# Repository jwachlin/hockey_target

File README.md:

# Interactive Electronic Hockey Targets
Hardware and firmware for interactive electronic hockey targets

To be used for hockey shooting training. More details at https://hackaday.io/project/169424-interactive-electronic-hockey-targets

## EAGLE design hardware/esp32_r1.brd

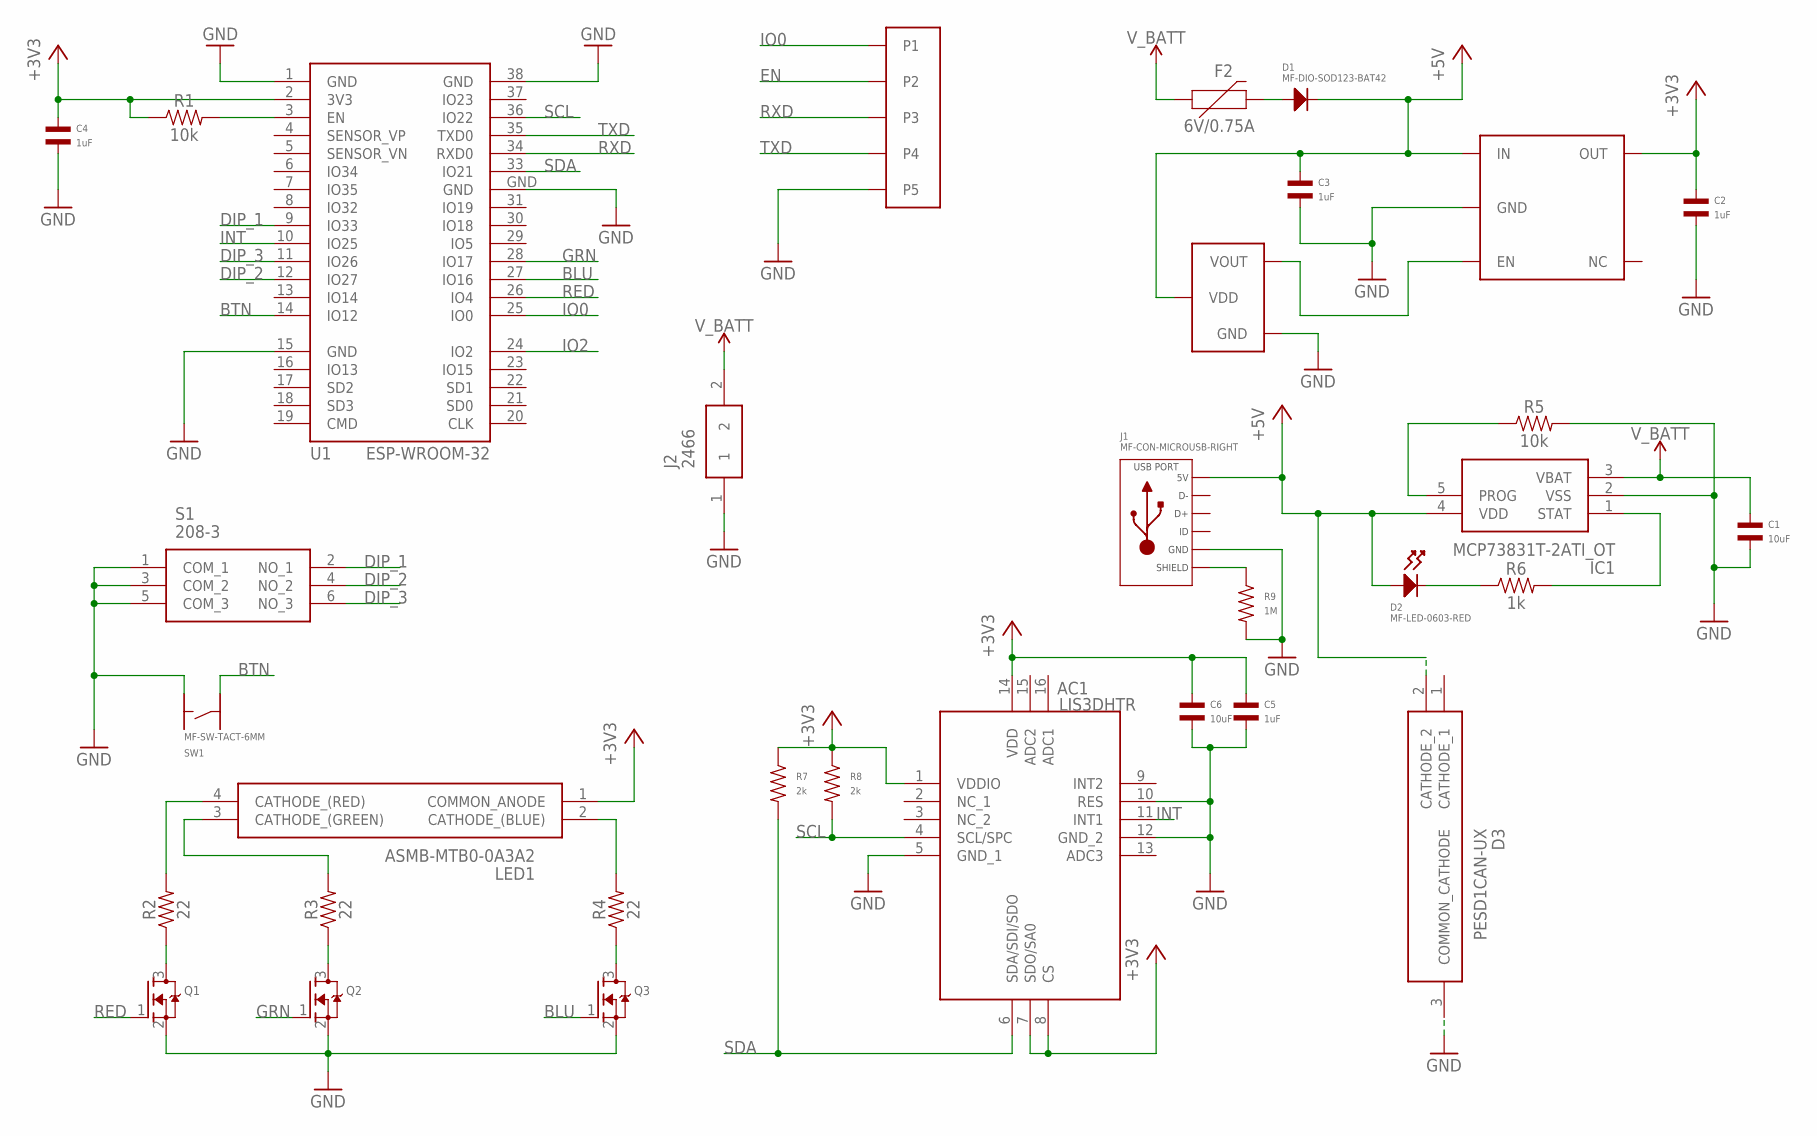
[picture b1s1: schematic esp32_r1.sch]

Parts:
AC1: LIS3DHTR; PQFN50P300X300X100-16N
C1, C6: 10uF; C1206
C2, C3, C4, C5: 1uF; C0402
D1: MF-DIO-SOD123-BAT42; SOD-123
D2: MF-LED-0603-RED; LED0603
D3: PESD1CAN-UX; SOT95P230X110-3N
F2: 6V/0.75A; 1206
IC1: MCP73831T-2ATI_OT; SOT95P270X145-5N
J1: MF-CON-MICROUSB-RIGHT; MICROUSB-RIGHT
J2: 2466
LED1: ASMB-MTB0-0A3A2; AVAGO_PLCC4
Q1, Q2, Q3: MOSFET-NREFLOW; SOT23-R
R1, R5: 10k; 0402
R2, R3, R4: 22; 0402
R6: 1k; 0402
R7, R8: 2k; R0402
R9: 1M; R0402
S1: 208-3; 2083
SW1: MF-SW-TACT-6MM; TACT6MM
U1: ESP-WROOM-32
U4: TLV755; SOT23-DBV
U6: 53047; PICOBLADE_53047
U7: BD49K33G; SSOP3

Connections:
+3V3: AC1.1 (VDDIO), AC1.7 (SDO/SA0), AC1.8 (CS), AC1.14 (VDD), C2.P$1, C4.P$1, C5.P$1, C6.P$1, LED1.1 (COMMON_ANODE), R1.1, R7.P$1, R8.P$1, U1.2 (3V3), U4.5 (OUT)
+5V: C3.P$1, D1.CATHODE, D2.ANODE, D3.2 (CATHODE_2), IC1.4 (VDD), J1.1 (5V), U4.1 (IN), U7.P$3 (VDD)
BLU: Q3.1 (G), U1.27 (IO16)
BTN: SW1.P$4, U1.14 (IO12)
DIP_1: S1.2 (NO_1), U1.9 (IO33)
DIP_2: S1.4 (NO_2), U1.12 (IO27)
DIP_3: S1.6 (NO_3), U1.11 (IO26)
EN: R1.2, U1.3 (EN), U6.P$2 (P2)
GND: AC1.5 (GND_1), AC1.10 (RES), AC1.12 (GND_2), C1.P$2, C2.P$2, C3.P$2, C4.P$2, C5.P$2, C6.P$2, D3.3 (COMMON_CATHODE), IC1.2 (VSS), J1.5 (GND), J2.1, Q1.2 (S), Q2.2 (S), Q3.2 (S), R5.2, R9.P$2, S1.1 (COM_1), S1.3 (COM_2), S1.5 (COM_3), SW1.P$2, U1.1 (GND), U1.15 (GND), U1.38 (GND), U1.GND, U4.2 (GND), U6.P$5 (P5), U7.P$1 (GND)
GRN: Q2.1 (G), U1.28 (IO17)
INT: AC1.11 (INT1), U1.10 (IO25)
IO0: U1.25 (IO0), U6.P$1 (P1)
IO2: U1.24 (IO2)
unnamed: U4.3 (EN), U7.P$2 (VOUT)
unnamed: LED1.4 (CATHODE_(RED)), R2.2
unnamed: Q1.3 (D), R2.1
unnamed: LED1.3 (CATHODE_(GREEN)), R3.2
unnamed: Q2.3 (D), R3.1
unnamed: LED1.2 (CATHODE_(BLUE)), R4.2
unnamed: Q3.3 (D), R4.1
unnamed: D1.ANODE, F2.2
unnamed: J1.S1 (SLD), J1.S2 (SLD), J1.S3 (SLD), J1.S4 (SLD), J1.S5 (SLD), J1.S6 (SLD), R9.P$1
unnamed: IC1.5 (PROG), R5.1
unnamed: D2.CATHODE, R6.1
unnamed: IC1.1 (STAT), R6.2
RED: Q1.1 (G), U1.26 (IO4)
RXD: U1.34 (RXD0), U6.P$3 (P3)
SCL: AC1.4 (SCL/SPC), R8.P$2, U1.36 (IO22)
SDA: AC1.6 (SDA/SDI/SDO), R7.P$2, U1.33 (IO21)
TXD: U1.35 (TXD0), U6.P$4 (P4)
V_BATT: C1.P$1, F2.1, IC1.3 (VBAT), J2.2

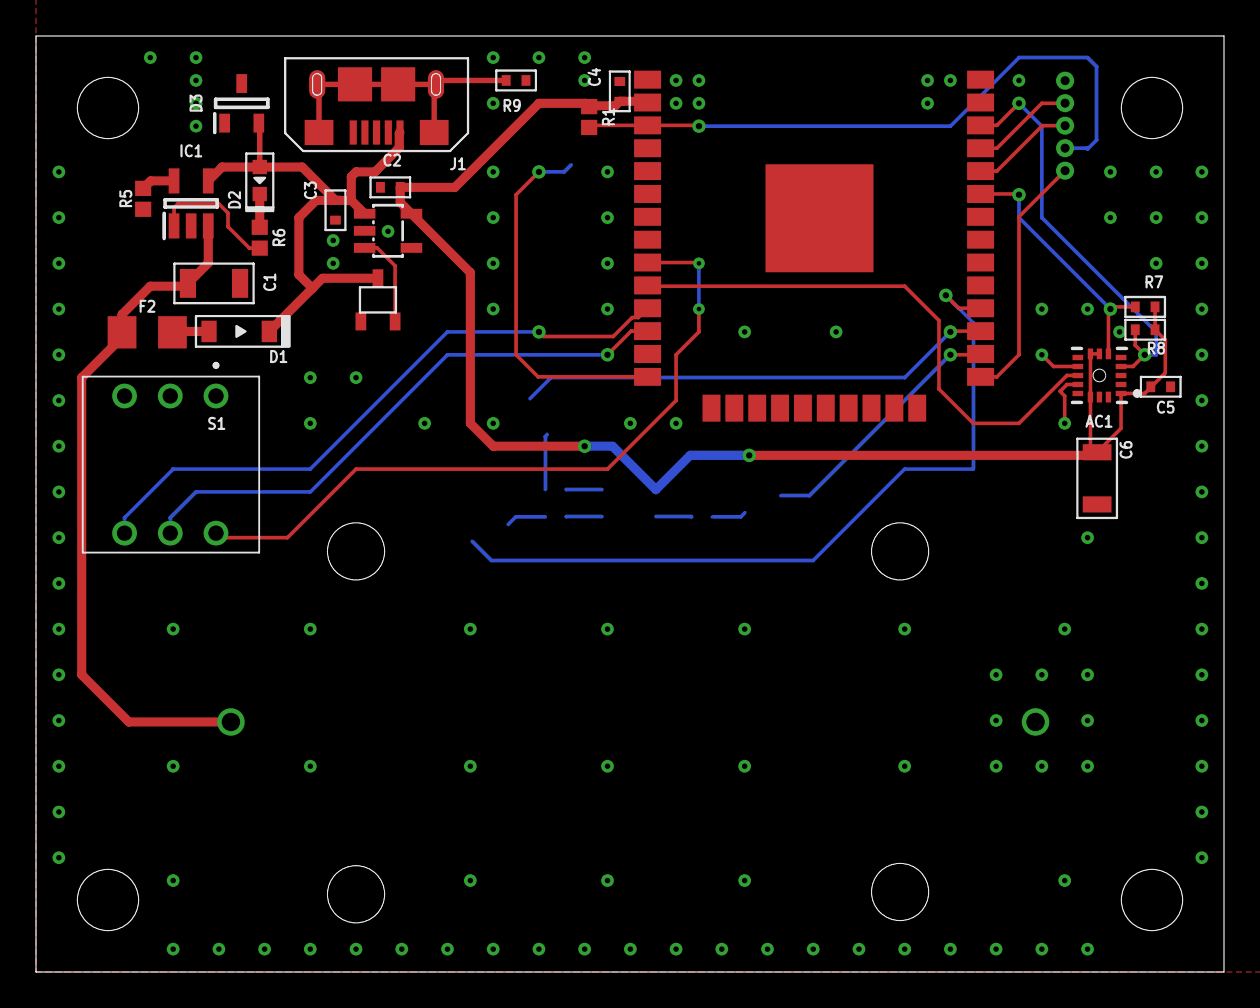
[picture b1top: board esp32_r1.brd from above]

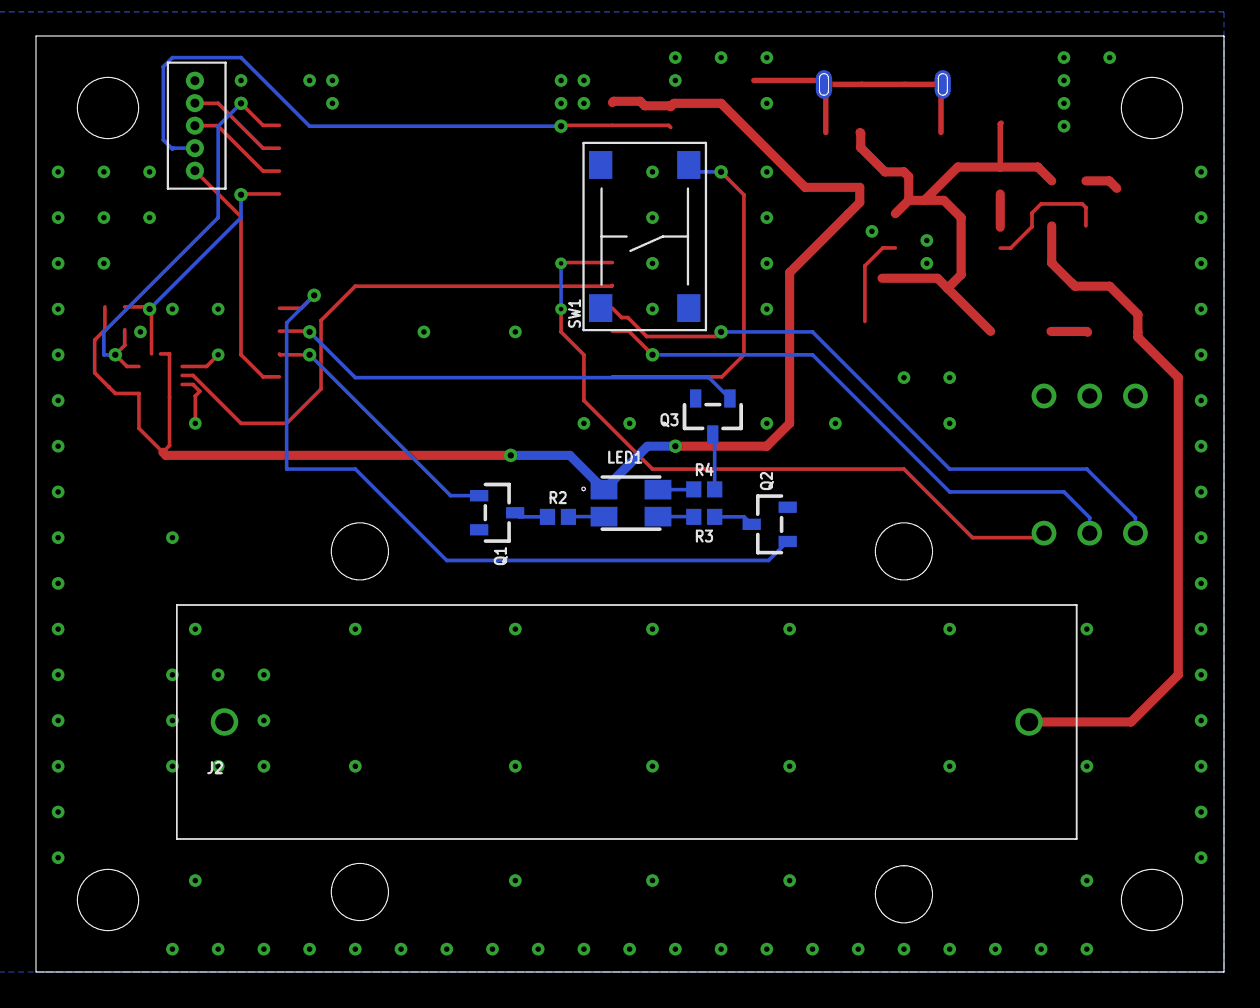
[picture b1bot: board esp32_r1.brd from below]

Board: 2 copper layers, 66.0 x 52.0 mm, 33 parts (10 on the bottom side), 30 nets.

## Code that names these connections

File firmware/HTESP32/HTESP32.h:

/*
MIT License

Copyright (c) 2020 by Jacob Wachlin

Permission is hereby granted, free of charge, to any person obtaining a copy
of this software and associated documentation files (the "Software"), to deal
in the Software without restriction, including without limitation the rights
to use, copy, modify, merge, publish, distribute, sublicense, and/or sell
copies of the Software, and to permit persons to whom the Software is
furnished to do so, subject to the following conditions:

The above copyright notice and this permission notice shall be included in all
copies or substantial portions of the Software.

THE SOFTWARE IS PROVIDED "AS IS", WITHOUT WARRANTY OF ANY KIND, EXPRESS OR
IMPLIED, INCLUDING BUT NOT LIMITED TO THE WARRANTIES OF MERCHANTABILITY,
FITNESS FOR A PARTICULAR PURPOSE AND NONINFRINGEMENT. IN NO EVENT SHALL THE
AUTHORS OR COPYRIGHT HOLDERS BE LIABLE FOR ANY CLAIM, DAMAGES OR OTHER
LIABILITY, WHETHER IN AN ACTION OF CONTRACT, TORT OR OTHERWISE, ARISING FROM,
OUT OF OR IN CONNECTION WITH THE SOFTWARE OR THE USE OR OTHER DEALINGS IN THE
SOFTWARE.
*/

/**
 * @file HTESP32.h
 * @author Jacob Wachlin
 * @date 13 February 2020
 * @brief ESP32 based hockey target
 */

#ifndef HTESP32_h
#define HTESP32_h

#define HT_DEBUG

#ifdef HT_DEBUG
#define debug_print(x)			Serial.print((x))
#else
#define debug_print(x)
#endif

#ifdef HT_DEBUG
#define debug_println(x)			Serial.println((x))
#else
#define debug_println(x)
#endif

//Pins
#define GRN_PIN 								17
#define BLU_PIN 								16
#define RED_PIN 								4
#define BTN_PIN									12
#define DIP1_PIN								33
#define DIP2_PIN								27
#define DIP3_PIN								26
#define SCL_PIN									22
#define SDA_PIN									21
#define INT_PIN									25

/**
 * @brief Performs initialization 
 *
 * 	This function setups up GPIO, I2C
 */
void begin();

/**
 * @brief Manages task
 *
 */
void task();
 
uint32_t get_index(void);

#endif

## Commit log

2020-03-14 Adds readme
2020-03-14 Updates readme
2020-03-14 Adds board designs and firmware for version 1 as built

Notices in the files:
parts and their libraries:
esp32: Creative Commons Attribution-ShareAlike 4.0 International
SparkFun-Resistors: Licensing: Creative Commons ShareAlike 4.0 International - https://creativecommons.org/licenses/by-sa/4.0
